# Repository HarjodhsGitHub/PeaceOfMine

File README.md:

# PeaceOfMine

## Start on the real car

With Docker installed, run these commands **on the car's onboard computer**:

```bash
git clone https://github.com/HarjodhsGitHub/PeaceOfMine.git
cd PeaceOfMine
util/build
util/run
```

Then **inside the container**, start the hardware stack:

```bash
ros2 launch peaceofmine_operator operator.launch.xml is_sim:=false
```

The image builds the workspace and sources it automatically when you enter
the container. No separate build or `source` command is needed for this setup.

On your laptop, connect to the car's Tailscale network and open
**[svea-mine.tailead4c5.ts.net:8080](http://svea-mine.tailead4c5.ts.net:8080)**.
Click **Take control**; driving requires ROS authority and PX4 arming through
the physical RC. A gamepad plugged into the laptop additionally requires HTTPS;
see the [operator guide](src/peaceofmine_operator/gui.md) for certificate setup.

Keep the wheels clear and the physical RC ready for the first launch. Verify the
saved calibration before moving the arm or probe. Stop with the physical RC,
then press `Ctrl+C` in the launch terminal.

## SVEA Starter Suite

ROS 2 Jazzy workspace for Small Vehicles for Autonomy (SVEA), with Python
interfaces, vehicle simulation and example controllers.

[Documentation](https://kth-sml.github.io/svea/) ·
[Tutorials](https://kth-sml.github.io/svea/tutorials/0_intro/) ·
[SVEA website](https://svea.eecs.kth.se)

## Installation

On macOS, we recommend [OrbStack](https://orbstack.dev/); Docker Desktop also
works. See [Docker setup](docs/setup/docker.md) for other platforms.
Then run on the host:

```bash
git clone https://github.com/KTH-SML/svea.git
cd svea
util/build
util/run
```

See [Docker setup](docs/setup/docker.md) for platform requirements and the
edit/build workflow, or [native installation](docs/development/native_build.md)
for Ubuntu 24.04.

## Run the simulation

Inside the container:

```bash
ros2 launch svea_examples floor2.launch.py
```

This starts two simulated vehicles and a Foxglove bridge. Open
[Foxglove](https://foxglove.dev/download), connect to `ws://localhost:8765`,
and import `foxglove/Floor2 Pure Pursuit.json` from the host checkout.

Continue with the [Floor 2 tutorial](docs/tutorials/1_floor2.md) to modify the
controller.

## PeaceOfMine operator

Build and source the workspace, then start the operator simulation:

```bash
ros2 launch peaceofmine_operator operator_sim.launch.py
```

Open the dashboard on port `8080`. For hardware setup, cameras, controls and
safety requirements, see the [operator guide](src/peaceofmine_operator/gui.md)
and [operator package](src/peaceofmine_operator/README.md).

## Use a vehicle

- [Hardware and assembly](docs/setup/hardware.md): vehicle overview and illustrated assembly manuals.
- [RC operation](docs/setup/rc_operation.md): controls, driving and shutdown.
- [ROS connection](docs/setup/ros_bringup.md): connect the onboard workspace to PX4.
- [MoCap localization](docs/mocap_localization.md): DISCOWER Qualisys setup.

## Related repositories

- [svea_parts](https://github.com/KTH-SML/svea_parts): CAD files, printable parts and assembly manuals.
- [SVEA-PX4-Autopilot documentation](https://github.com/nilskiefer/SVEA-PX4-Autopilot/blob/8e17861fa85809fecdbdddea035b0fa49264517a/docs/en/svea/index.md): firmware setup, flashing, troubleshooting and PMB3 reference.

## Contributing

See [CONTRIBUTING.md](CONTRIBUTING.md) for commit and pull-request conventions.

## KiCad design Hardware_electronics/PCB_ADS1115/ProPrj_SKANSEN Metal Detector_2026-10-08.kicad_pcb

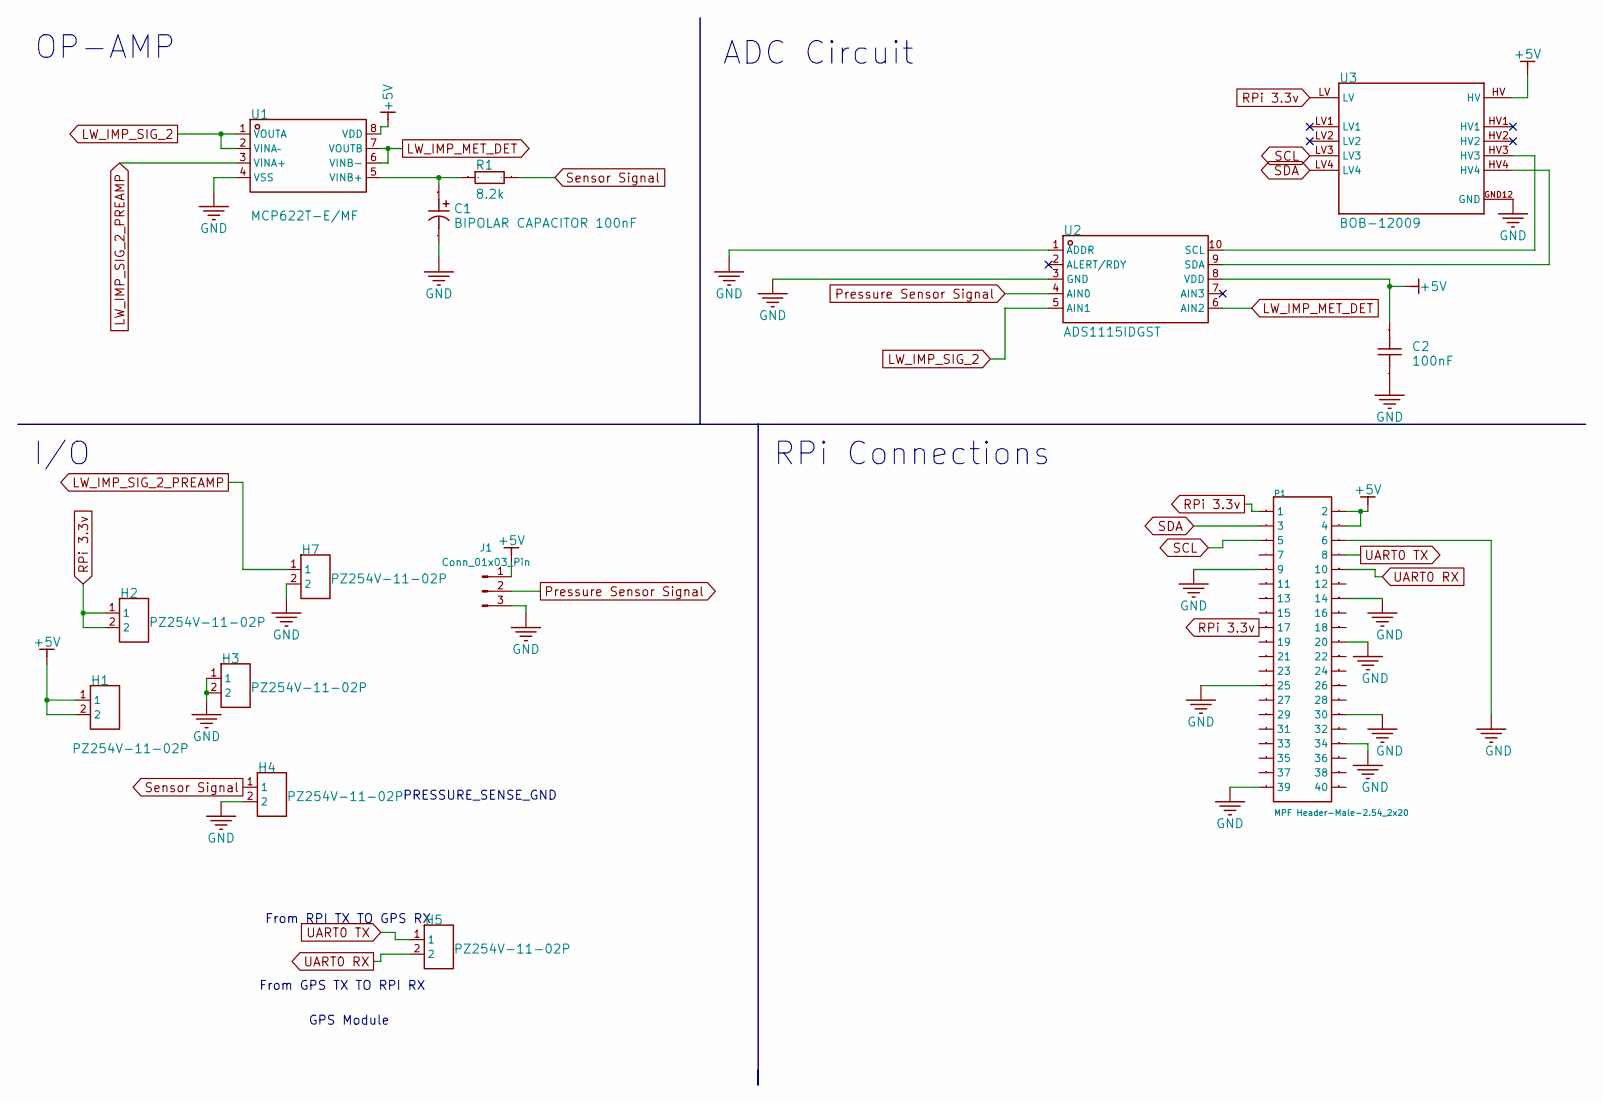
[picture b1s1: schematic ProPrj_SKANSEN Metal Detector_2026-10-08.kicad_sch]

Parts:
C1: BIPOLAR CAPACITOR 100nF; CAP-TH_BD13.0-P5.00-D0.6-FD; Manufacturer Part BIPOLAR CAPACITOR 47,0 UF; LCSC Part Name BIPOLAR CAPACITOR 47,0 UF
C2: 100nF; C0805
H1, H2, H3, H4, H5, H7: PZ254V-11-02P; HDR-TH_2P-P2.54-V-M; Current Rating 3A; Voltage Rating (Max) 250V; Manufacturer Part PZ254V-11-02P; LCSC Part Name 1x2P 间距:2.54mm 方针 直插
J1: Conn_01x03_Pin; PinSocket_1x03_P2.54mm_Vertical
P1: MPF Header-Male-2.54_2x20; HDR-TH_40PIN-V-ROW2-COL20-FEMALE-PITCH2.54; Manufacturer Part 2.54mm 2*20P male header
R1: 8.2k; R1206
U1: MCP622T-E/MF; MCP622-breakout; Manufacturer Part MCP622T-E/MF; LCSC Part Name MCP622T-E/MF
U2: ADS1115IDGST; HDR-TH_10P-P2.54-V-F-S2.54; Voltage - Supply 2V~5.5V; Voltage Reference Built-in; Manufacturer Part ADS1115IDGST; LCSC Part Name 具有内部基准、振荡器和可编程比较器且兼容 I2C 的ADS111x、超小型、低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
U3: BOB-12009; CONV_BOB-12009

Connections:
+5V: C2.2, H1.1, H1.2, J1.1, P1.2, P1.4, U1.8 (VDD), U2.8 (VDD), U3.HV
GND: C1.2, C2.1, H3.1, H3.2, H4.2, H7.2, J1.3, P1.6, P1.9, P1.14, P1.20, P1.25, P1.30, P1.34, P1.39, U1.4 (VSS), U2.1 (ADDR), U2.3 (GND), U3.GND12 (GND)
LW_IMP_MET_DET: U1.6 (VINB-), U1.7 (VOUTB), U2.6 (AIN2)
LW_IMP_SIG_2: U1.1 (VOUTA), U1.2 (VINA–), U2.5 (AIN1)
LW_IMP_SIG_2_PREAMP: H7.1, U1.3 (VINA+)
unnamed: C1.1, R1.1, U1.5 (VINB+)
unnamed: U2.10 (SCL), U3.HV3
unnamed: U2.9 (SDA), U3.HV4
Pressure Sensor Signal: J1.2, U2.4 (AIN0)
RPi 3.3v: H2.1, H2.2, P1.1, P1.17, U3.LV
SCL: P1.5, U3.LV3
SDA: P1.3, U3.LV4
Sensor Signal: H4.1, R1.2
UART0 RX: H5.2, P1.10
UART0 TX: H5.1, P1.8

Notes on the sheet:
RPi Connections
PRESSURE_SENSE_GND
ADC Circuit
GPS Module
From GPS TX TO RPI RX
From RPI TX TO GPS RX
OP-AMP
I/O

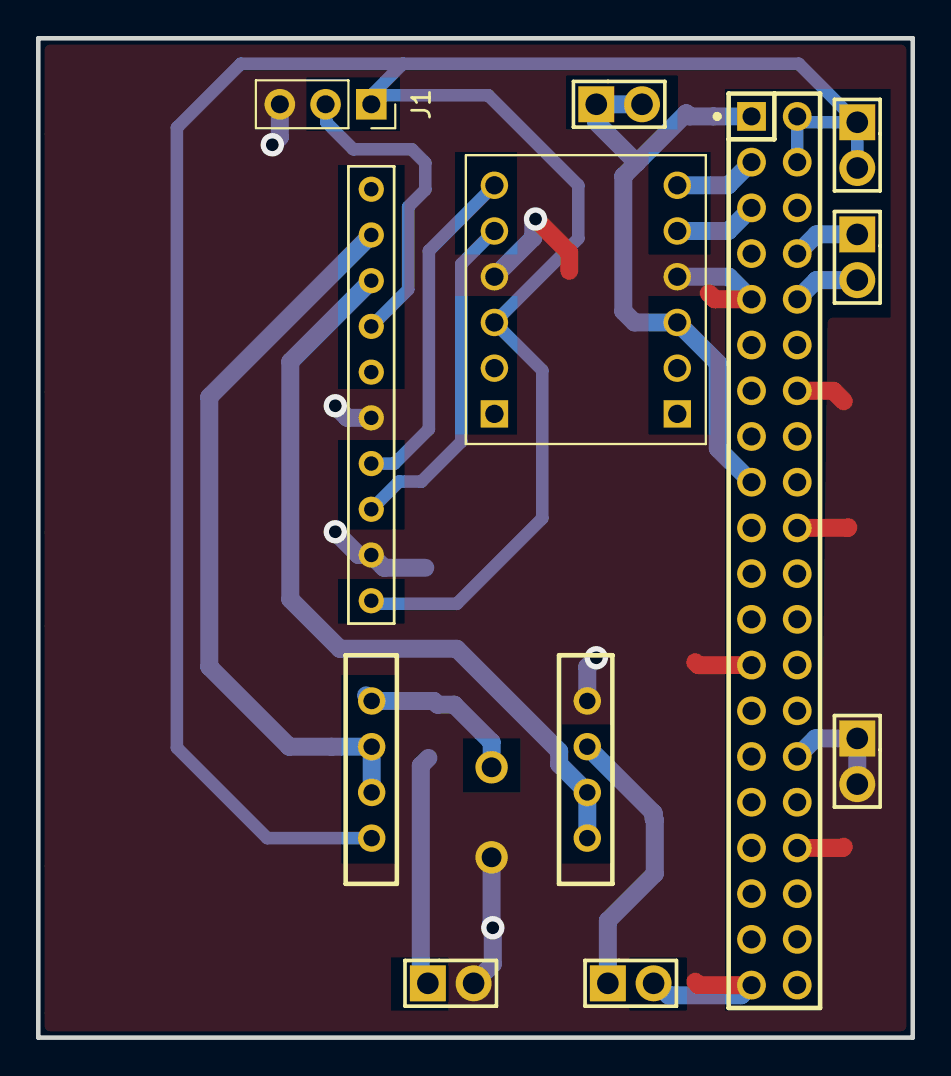
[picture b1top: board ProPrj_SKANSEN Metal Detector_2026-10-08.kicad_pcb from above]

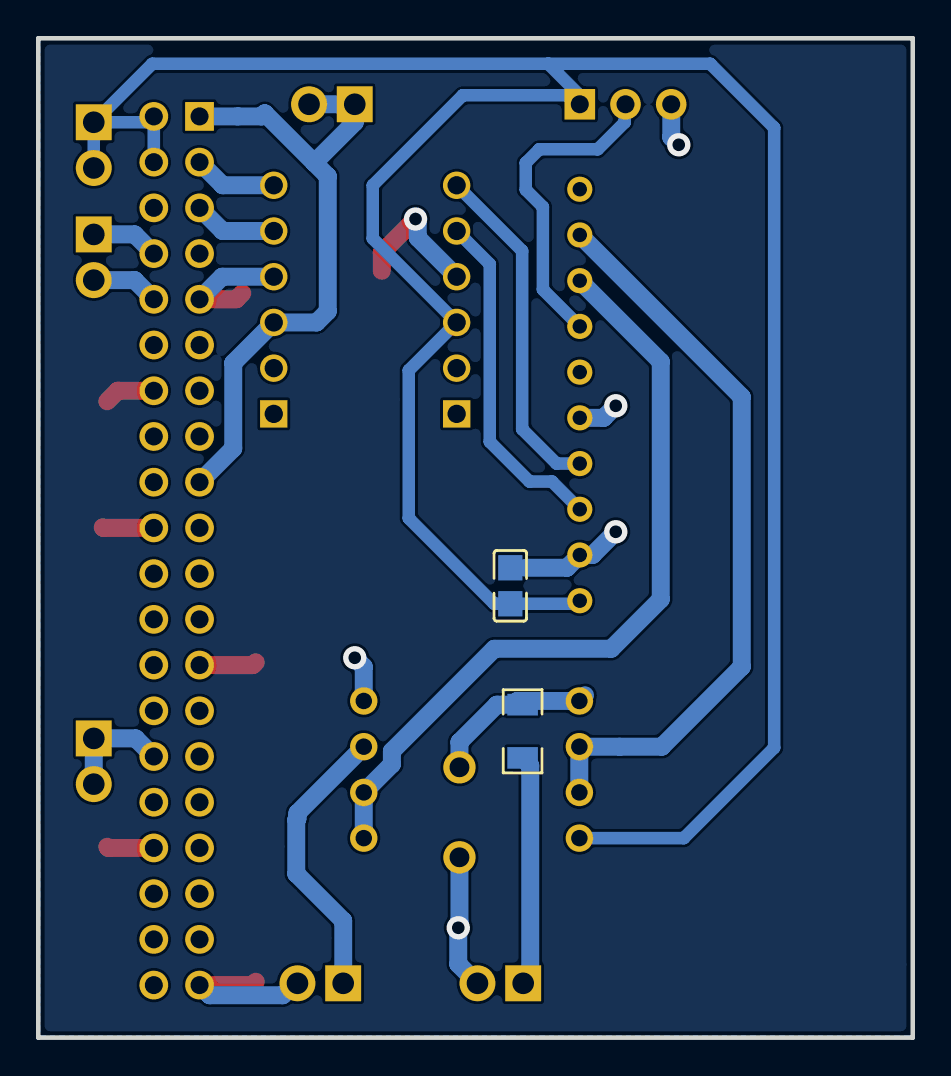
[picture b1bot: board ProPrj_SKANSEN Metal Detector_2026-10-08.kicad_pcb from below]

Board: 2 copper layers, 48.6 x 55.5 mm, 14 parts (2 on the bottom side), 15 nets.
